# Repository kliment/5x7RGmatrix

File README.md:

Replaces 7x5 RG matrix.

For column anode, row cathode (CARC) use ledarray.kicad_pcb

For row anode, column cathode (RACC) use ledarray-ca.kicad_pcb

LEDs are https://lcsc.com/product-detail/Light-Emitting-Diodes-LED_SMDLED-120-480mcd_C110903.html

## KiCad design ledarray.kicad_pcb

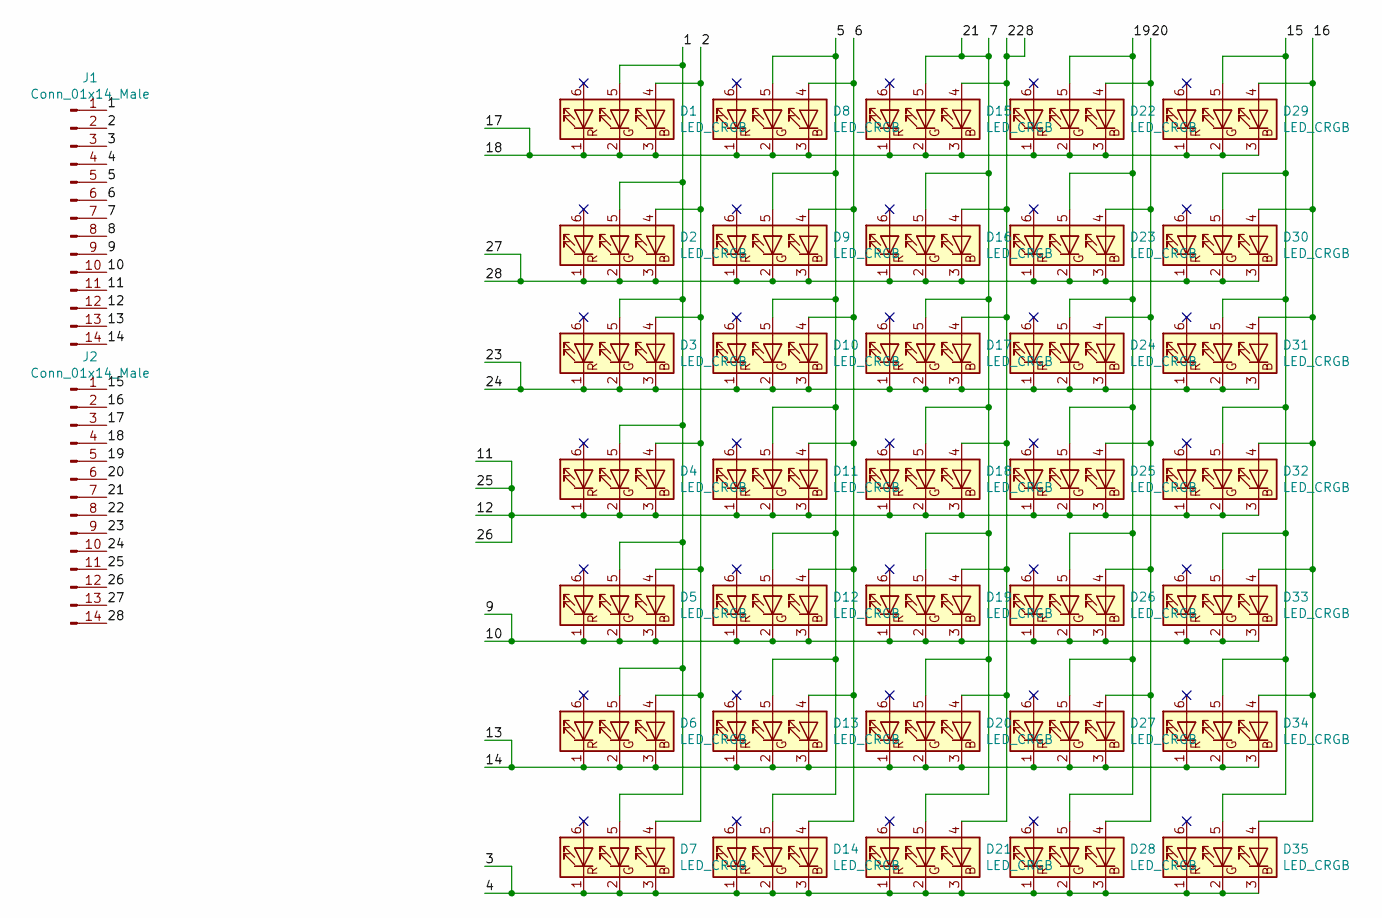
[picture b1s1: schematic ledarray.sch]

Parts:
D1, D2, D3, D4, D5, D6, D7, D8, D9, D10, D11, D12, D13, D14, D15, D16, D17, D18, D19, D20, D21, D22, D23, D24, D25, D26, D27, D28, D29, D30, D31, D32, D33, D34, D35: LED_CRGB; FM-Z3535RGBA-SH
J1, J2: Conn_01x14_Male; PinHeader_1x14_P2.54mm_Vertical

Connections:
/1: D1.5 (GA), D2.5 (GA), D3.5 (GA), D4.5 (GA), D5.5 (GA), D6.5 (GA), D7.5 (GA), J1.1
/2: D1.4 (BA), D2.4 (BA), D3.4 (BA), D4.4 (BA), D5.4 (BA), D6.4 (BA), D7.4 (BA), J1.2
/3: D7.1 (RK), D7.2 (GK), D7.3 (BK), D14.1 (RK), D14.2 (GK), D14.3 (BK), D21.1 (RK), D21.2 (GK), D21.3 (BK), D28.1 (RK), D28.2 (GK), D28.3 (BK), D35.1 (RK), D35.2 (GK), D35.3 (BK), J1.3, J1.4
/5: D8.5 (GA), D9.5 (GA), D10.5 (GA), D11.5 (GA), D12.5 (GA), D13.5 (GA), D14.5 (GA), J1.5
/6: D8.4 (BA), D9.4 (BA), D10.4 (BA), D11.4 (BA), D12.4 (BA), D13.4 (BA), D14.4 (BA), J1.6
/10: D5.1 (RK), D5.2 (GK), D5.3 (BK), D12.1 (RK), D12.2 (GK), D12.3 (BK), D19.1 (RK), D19.2 (GK), D19.3 (BK), D26.1 (RK), D26.2 (GK), D26.3 (BK), D33.1 (RK), D33.2 (GK), D33.3 (BK), J1.9, J1.10
/11: D4.1 (RK), D4.2 (GK), D4.3 (BK), D11.1 (RK), D11.2 (GK), D11.3 (BK), D18.1 (RK), D18.2 (GK), D18.3 (BK), D25.1 (RK), D25.2 (GK), D25.3 (BK), D32.1 (RK), D32.2 (GK), D32.3 (BK), J1.11, J1.12, J2.11, J2.12
/13: D6.1 (RK), D6.2 (GK), D6.3 (BK), D13.1 (RK), D13.2 (GK), D13.3 (BK), D20.1 (RK), D20.2 (GK), D20.3 (BK), D27.1 (RK), D27.2 (GK), D27.3 (BK), D34.1 (RK), D34.2 (GK), D34.3 (BK), J1.13, J1.14
/15: D29.5 (GA), D30.5 (GA), D31.5 (GA), D32.5 (GA), D33.5 (GA), D34.5 (GA), D35.5 (GA), J2.1
/16: D29.4 (BA), D30.4 (BA), D31.4 (BA), D32.4 (BA), D33.4 (BA), D34.4 (BA), D35.4 (BA), J2.2
/17: D1.1 (RK), D1.2 (GK), D1.3 (BK), D8.1 (RK), D8.2 (GK), D8.3 (BK), D15.1 (RK), D15.2 (GK), D15.3 (BK), D22.1 (RK), D22.2 (GK), D22.3 (BK), D29.1 (RK), D29.2 (GK), D29.3 (BK), J2.3, J2.4
/19: D22.5 (GA), D23.5 (GA), D24.5 (GA), D25.5 (GA), D26.5 (GA), D27.5 (GA), D28.5 (GA), J2.5
/20: D22.4 (BA), D23.4 (BA), D24.4 (BA), D25.4 (BA), D26.4 (BA), D27.4 (BA), D28.4 (BA), J2.6
/21: D15.5 (GA), D16.5 (GA), D17.5 (GA), D18.5 (GA), D19.5 (GA), D20.5 (GA), D21.5 (GA), J1.7, J2.7
/22: D15.4 (BA), D16.4 (BA), D17.4 (BA), D18.4 (BA), D19.4 (BA), D20.4 (BA), D21.4 (BA), J1.8, J2.8
/23: D3.1 (RK), D3.2 (GK), D3.3 (BK), D10.1 (RK), D10.2 (GK), D10.3 (BK), D17.1 (RK), D17.2 (GK), D17.3 (BK), D24.1 (RK), D24.2 (GK), D24.3 (BK), D31.1 (RK), D31.2 (GK), D31.3 (BK), J2.9, J2.10
/27: D2.1 (RK), D2.2 (GK), D2.3 (BK), D9.1 (RK), D9.2 (GK), D9.3 (BK), D16.1 (RK), D16.2 (GK), D16.3 (BK), D23.1 (RK), D23.2 (GK), D23.3 (BK), D30.1 (RK), D30.2 (GK), D30.3 (BK), J2.13, J2.14

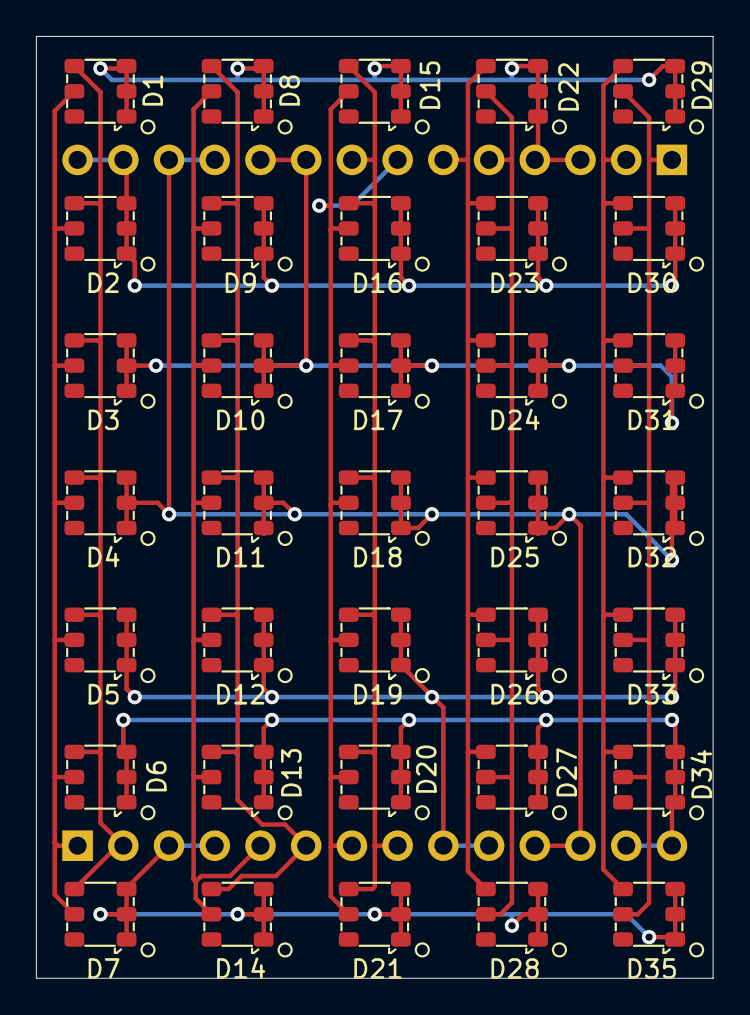
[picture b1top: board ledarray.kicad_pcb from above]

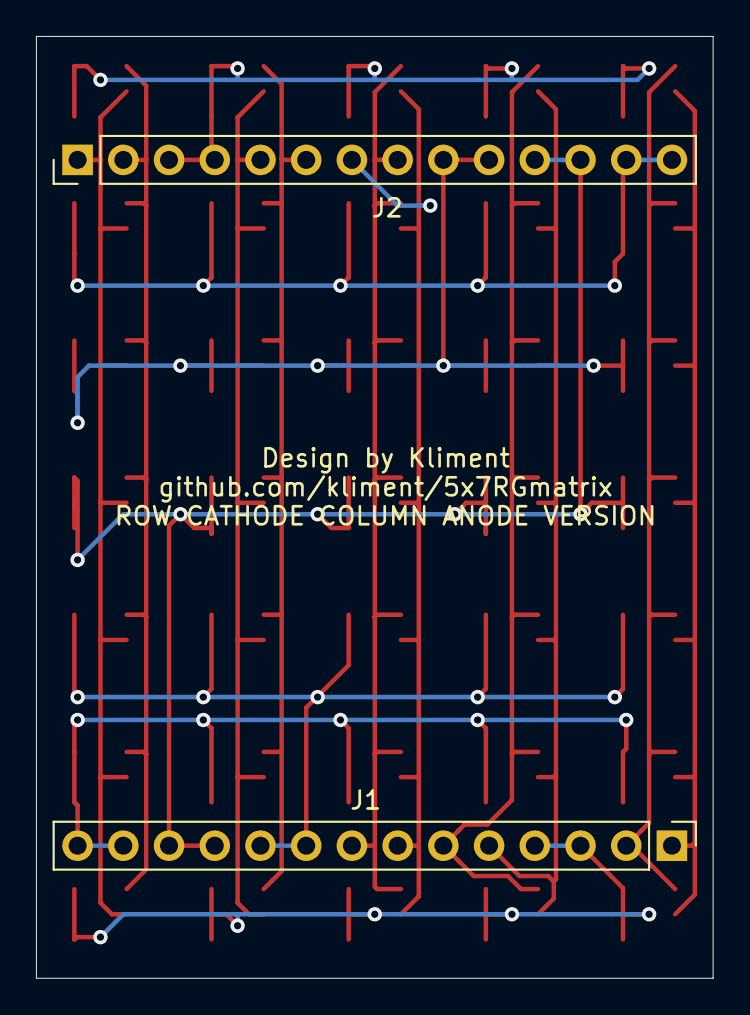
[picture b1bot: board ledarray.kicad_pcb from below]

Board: 2 copper layers, 37.6 x 52.3 mm, 37 parts (2 on the bottom side), 17 nets.

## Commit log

2019-07-17 Added readme
2019-07-17 Update README
    Add image
2019-07-18 Add reversed LED polarity variant
